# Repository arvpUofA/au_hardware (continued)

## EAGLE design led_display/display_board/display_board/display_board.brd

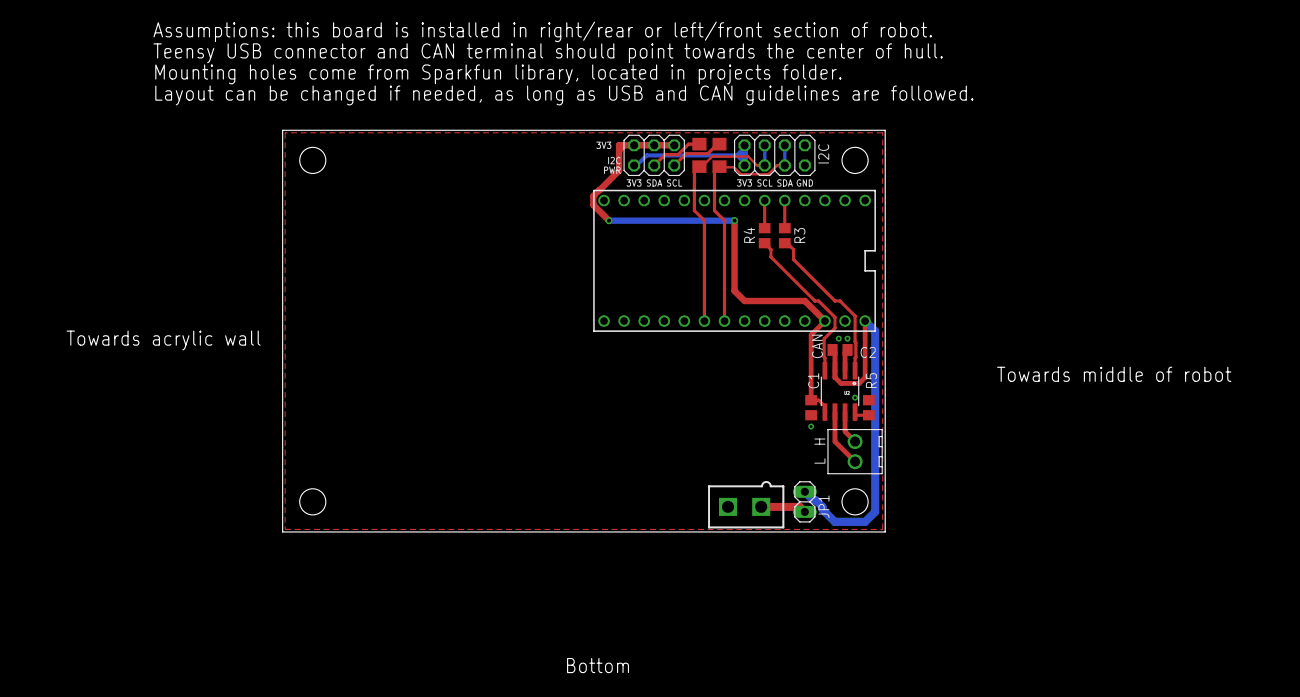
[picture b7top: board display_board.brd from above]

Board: 2 copper layers, 76.2 x 50.8 mm, 18 parts (0 on the bottom side), 16 nets.

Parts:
C1, C2: 10u; C0805
CON1: MOLEX_5566-2; 5566-2
JP1: 1X02
JP2: 2X03
JP3: 2X04
R1, R2: 10k; R1206
R3, R4: 220; R0805
R5: 1k; R0805
U1: TEENSY_3.1_BASIC_2
U2: TCAN1042HVDR; SOIC8
U$1, U$2, U$3, U$4: STAND-OFF
X1: OSTVN02A150

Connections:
+3V3: C1.1, JP2.1, JP2.3, JP2.5, U1.3.3V, U2.5
+5V: CON1.1, JP1.2
CANH: U2.7, X1.P$2
CANL: U2.6, X1.P$1
CAN_RX: R4.2, U2.4
CAN_RX_T: R4.1, U1.4
CAN_TX: R3.2, U2.1
CAN_TX_T: R3.1, U1.3
GND: C1.2, C2.2, CON1.2, JP3.1, JP3.2, R5.1, U1.GND, U2.2
I2_3V3: JP2.6, JP3.7, JP3.8
SCL: JP3.5, JP3.6, R2.2, U1.18/A4
SCL_3V3: JP2.2, R1.1
SDA: JP3.3, JP3.4, R1.2, U1.19/A5
SDA_3V3: JP2.4, R2.1
STB: R5.2, U2.8
VIN: C2.1, JP1.1, U1.VIN, U2.3
